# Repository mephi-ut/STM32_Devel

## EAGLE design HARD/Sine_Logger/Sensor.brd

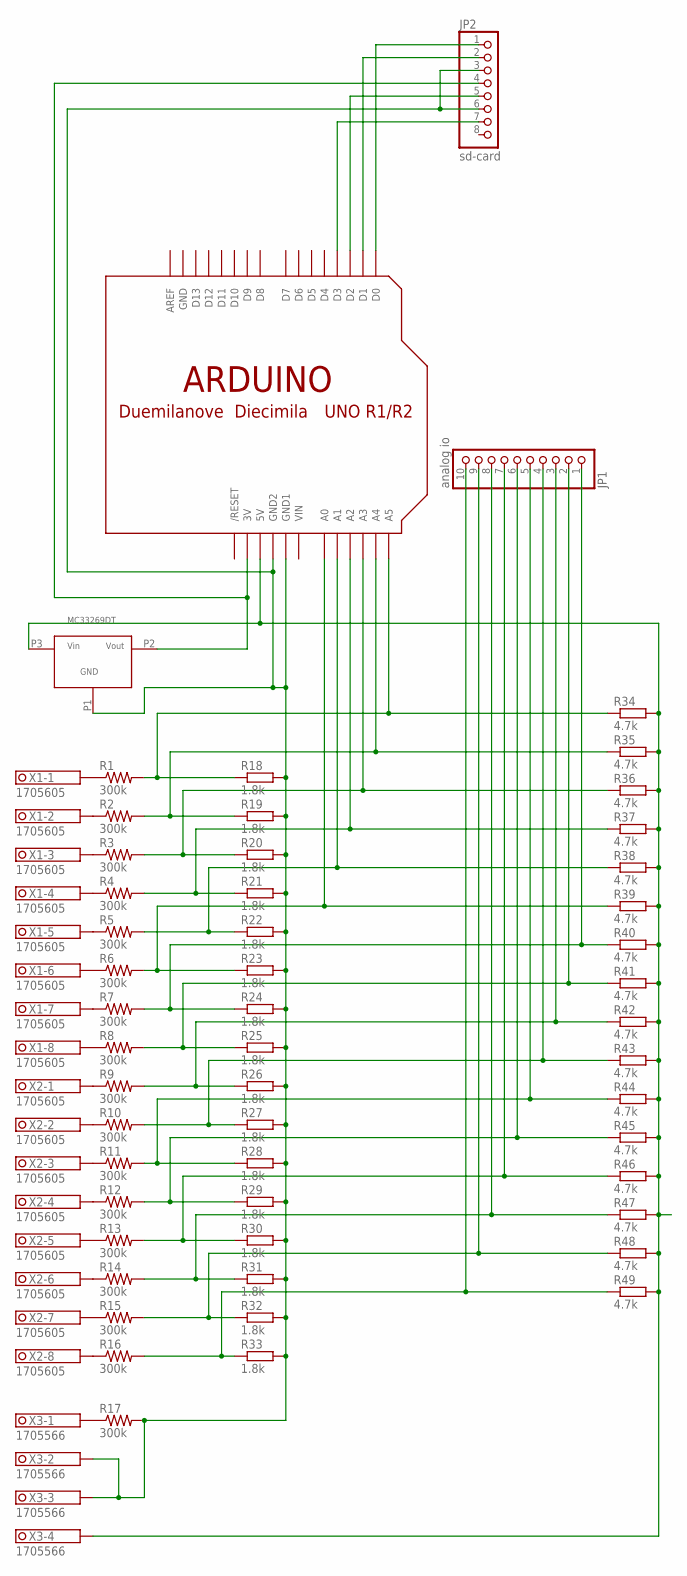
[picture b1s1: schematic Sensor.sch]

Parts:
JP1: analog io; 1X10
JP2: sd-card; 1X08
R1, R2, R3, R4, R5, R6, R7, R8, R9, R10, R11, R12, R13, R14, R15, R16, R17: 300k; 0207/15
R18, R19, R20, R21, R22, R23, R24, R25, R26, R27, R28, R29, R30, R31, R32, R33: 1.8k; R1206
R34, R35, R36, R37, R38, R39, R40, R41, R42, R43, R44, R45, R46, R47, R48, R49: 4.7k; R1206
U$1: MC33269DT
U$2: ARDUINOUNO; ARDUINO
X1, X2: 1705605
X3: 1705566

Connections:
GND: U$2.GND
unnamed: R1.1, X1.1.1, X1.1.2
unnamed: R2.1, X1.2.1, X1.2.2
unnamed: R3.1, X1.3.1, X1.3.2
unnamed: R4.1, X1.4.1, X1.4.2
unnamed: R5.1, X1.5.1, X1.5.2
unnamed: R6.1, X1.6.1, X1.6.2
unnamed: R7.1, X1.7.1, X1.7.2
unnamed: R8.1, X1.8.1, X1.8.2
unnamed: R9.1, X2.1.1, X2.1.2
unnamed: R10.1, X2.2.1, X2.2.2
unnamed: R11.1, X2.3.1, X2.3.2
unnamed: R12.1, X2.4.1, X2.4.2
unnamed: R13.1, X2.5.1, X2.5.2
unnamed: R14.1, X2.6.1, X2.6.2
unnamed: R15.1, X2.7.1, X2.7.2
unnamed: R16.1, X2.8.1, X2.8.2
unnamed: R17.1, X3.1.1, X3.1.2
unnamed: R1.2, R18.1, R34.1, U$2.A5
unnamed: R2.2, R19.1, R35.1, U$2.A4
unnamed: R3.2, R20.1, R36.1, U$2.A3
unnamed: R4.2, R21.1, R37.1, U$2.A2
unnamed: R5.2, R22.1, R38.1, U$2.A1
unnamed: R6.2, R23.1, R39.1, U$2.A0
unnamed: JP1.1, R7.2, R24.1, R40.1
unnamed: JP1.2, R8.2, R25.1, R41.1
unnamed: JP1.3, R9.2, R26.1, R42.1
unnamed: JP1.4, R10.2, R27.1, R43.1
unnamed: JP1.5, R11.2, R28.1, R44.1
unnamed: JP1.6, R12.2, R29.1, R45.1
unnamed: JP1.7, R13.2, R30.1, R46.1
unnamed: JP1.8, R14.2, R31.1, R47.1
unnamed: JP1.9, R15.2, R32.1, R48.1
unnamed: JP1.10, R16.2, R33.1, R49.1
unnamed: R34.2, R35.2, R36.2, R37.2, R38.2, R39.2, R40.2, R41.2, R42.2, R43.2, R44.2, R45.2, R46.2, R47.2, R48.2, R49.2, U$1.P3 (VIN), U$2.5V, X3.4.1, X3.4.2
unnamed: JP2.1, U$2.D0
unnamed: JP2.2, U$2.D1
unnamed: JP2.5, U$2.D2
unnamed: JP2.7, U$2.D3
unnamed: JP2.4, U$1.P2 (VOUT), U$2.3V
unnamed: JP2.3, JP2.6, R17.2, R18.2, R19.2, R20.2, R21.2, R22.2, R23.2, R24.2, R25.2, R26.2, R27.2, R28.2, R29.2, R30.2, R31.2, R32.2, R33.2, U$1.P1 (GND), U$2.GND1, U$2.GND2, X3.2.1, X3.2.2, X3.3.1, X3.3.2
VIN: U$2.VIN

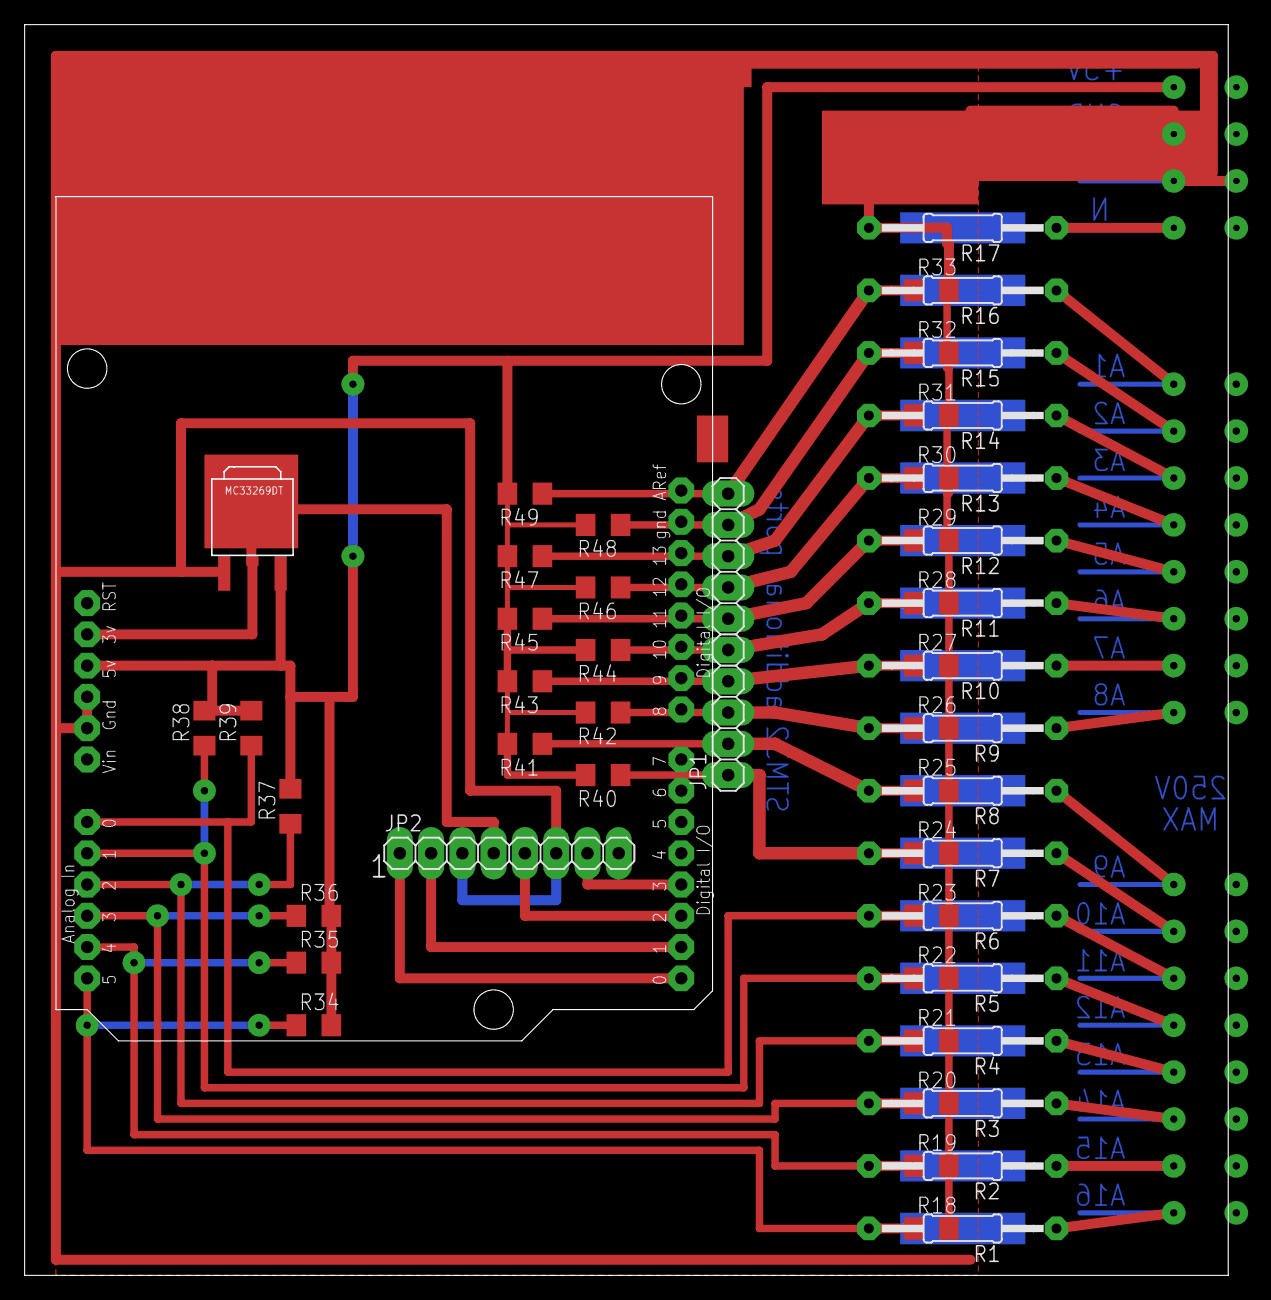
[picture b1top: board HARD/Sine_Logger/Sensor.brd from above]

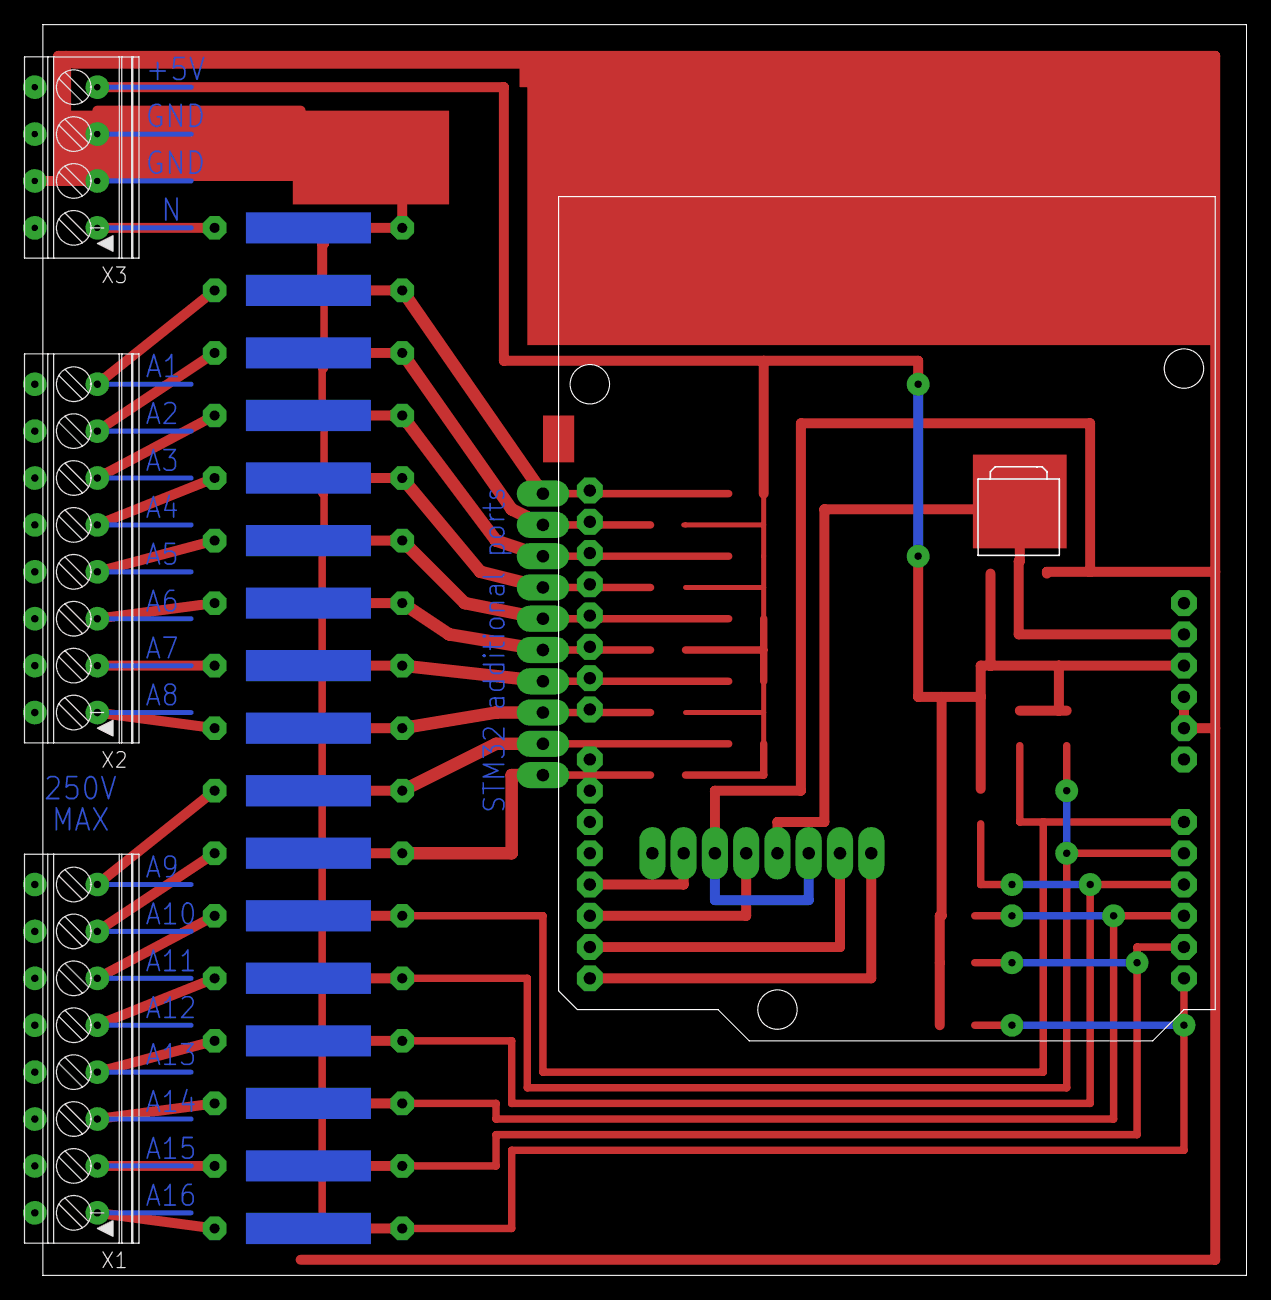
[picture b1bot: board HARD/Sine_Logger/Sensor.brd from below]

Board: 2 copper layers, 97.8 x 101.6 mm, 56 parts (3 on the bottom side), 40 nets.

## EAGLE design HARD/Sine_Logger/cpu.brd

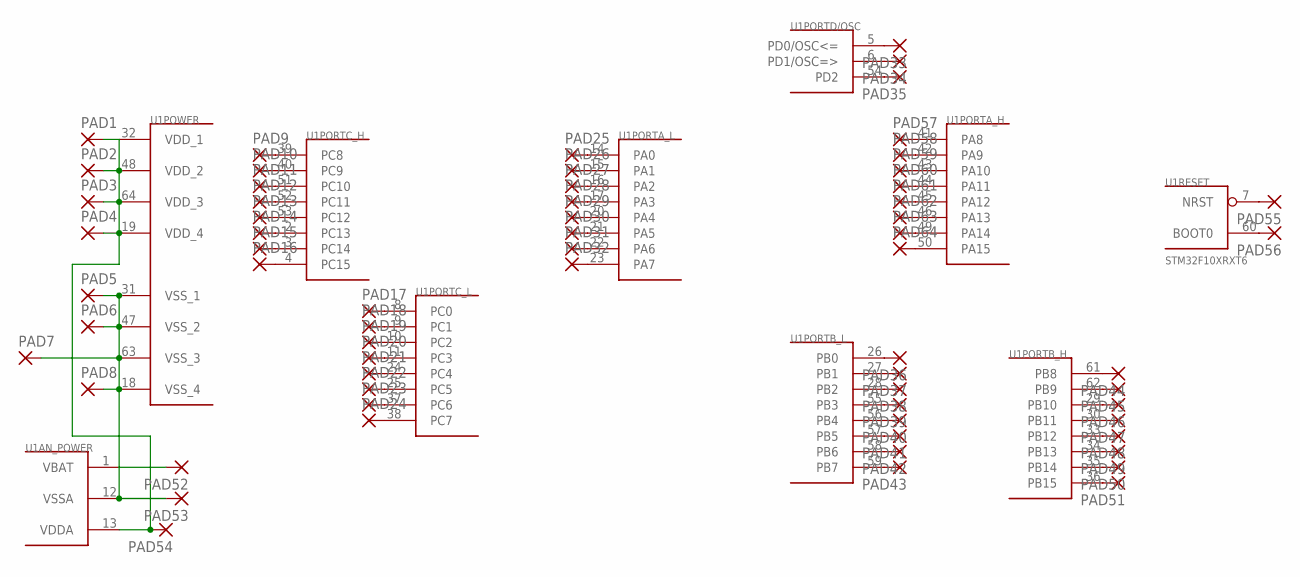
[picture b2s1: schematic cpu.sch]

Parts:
PAD1, PAD2, PAD3, PAD4, PAD5, PAD6, PAD7, PAD8, PAD9, PAD10, PAD11, PAD12, PAD13, PAD14, PAD15, PAD16, PAD17, PAD18, PAD19, PAD20, PAD21, PAD22, PAD23, PAD24, PAD25, PAD26, PAD27, PAD28, PAD29, PAD30, PAD31, PAD32, PAD33, PAD34, PAD35, PAD36, PAD37, PAD38, PAD39, PAD40, PAD41, PAD42, PAD43, PAD44, PAD45, PAD46, PAD47, PAD48, PAD49, PAD50, PAD51, PAD52, PAD53, PAD54, PAD55, PAD56, PAD57, PAD58, PAD59, PAD60, PAD61, PAD62, PAD63, PAD64: SMD2; SMD1,27-2,54
U1: STM32F10XRXT6; TQFP64

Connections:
unnamed: PAD1.1, PAD2.1, PAD3.1, PAD4.1, PAD54.1, U1.13 (VDDA), U1.19 (VDD_4), U1.32 (VDD_1), U1.48 (VDD_2), U1.64 (VDD_3)
unnamed: PAD57.1, U1.41 (PA8)
unnamed: PAD58.1, U1.42 (PA9)
unnamed: PAD59.1, U1.43 (PA10)
unnamed: PAD5.1, PAD6.1, PAD7.1, PAD8.1, PAD53.1, U1.12 (VSSA), U1.18 (VSS_4), U1.31 (VSS_1), U1.47 (VSS_2), U1.63 (VSS_3)
unnamed: PAD60.1, U1.44 (PA11)
unnamed: PAD61.1, U1.45 (PA12)
unnamed: PAD62.1, U1.46 (PA13)
unnamed: PAD9.1, U1.39 (PC8)
unnamed: PAD10.1, U1.40 (PC9)
unnamed: PAD11.1, U1.51 (PC10)
unnamed: PAD12.1, U1.52 (PC11)
unnamed: PAD13.1, U1.53 (PC12)
unnamed: PAD14.1, U1.2 (PC13)
unnamed: PAD15.1, U1.3 (PC14)
unnamed: PAD16.1, U1.4 (PC15)
unnamed: PAD17.1, U1.8 (PC0)
unnamed: PAD18.1, U1.9 (PC1)
unnamed: PAD19.1, U1.10 (PC2)
unnamed: PAD20.1, U1.11 (PC3)
unnamed: PAD21.1, U1.24 (PC4)
unnamed: PAD22.1, U1.25 (PC5)
unnamed: PAD23.1, U1.37 (PC6)
unnamed: PAD24.1, U1.38 (PC7)
unnamed: PAD25.1, U1.14 (PA0)
unnamed: PAD26.1, U1.15 (PA1)
unnamed: PAD27.1, U1.16 (PA2)
unnamed: PAD28.1, U1.17 (PA3)
unnamed: PAD29.1, U1.20 (PA4)
unnamed: PAD30.1, U1.21 (PA5)
unnamed: PAD31.1, U1.22 (PA6)
unnamed: PAD32.1, U1.23 (PA7)
unnamed: PAD33.1, U1.5 (PD0/OSC<=)
unnamed: PAD34.1, U1.6 (PD1/OSC=>)
unnamed: PAD35.1, U1.54 (PD2)
unnamed: PAD36.1, U1.26 (PB0)
unnamed: PAD37.1, U1.27 (PB1)
unnamed: PAD38.1, U1.28 (PB2)
unnamed: PAD39.1, U1.55 (PB3)
unnamed: PAD40.1, U1.56 (PB4)
unnamed: PAD41.1, U1.57 (PB5)
unnamed: PAD42.1, U1.58 (PB6)
unnamed: PAD43.1, U1.59 (PB7)
unnamed: PAD44.1, U1.61 (PB8)
unnamed: PAD45.1, U1.62 (PB9)
unnamed: PAD46.1, U1.29 (PB10)
unnamed: PAD47.1, U1.30 (PB11)
unnamed: PAD48.1, U1.33 (PB12)
unnamed: PAD49.1, U1.34 (PB13)
unnamed: PAD50.1, U1.35 (PB14)
unnamed: PAD51.1, U1.36 (PB15)
unnamed: PAD52.1, U1.1 (VBAT)
unnamed: PAD63.1, U1.49 (PA14)
unnamed: PAD64.1, U1.50 (PA15)
unnamed: PAD55.1, U1.7 (NRST)
unnamed: PAD56.1, U1.60 (BOOT0)

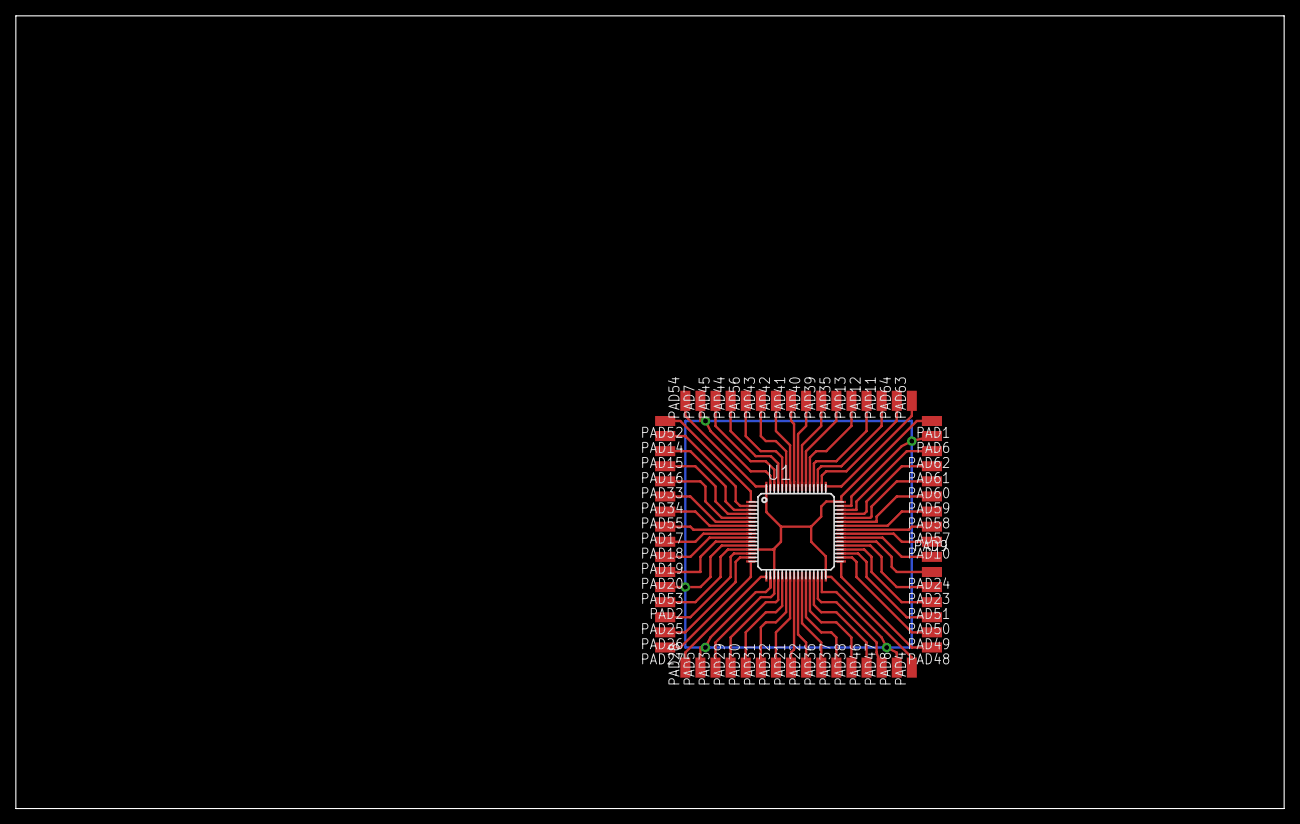
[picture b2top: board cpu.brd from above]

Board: 2 copper layers, 160.0 x 100.0 mm, 65 parts (0 on the bottom side), 56 nets.

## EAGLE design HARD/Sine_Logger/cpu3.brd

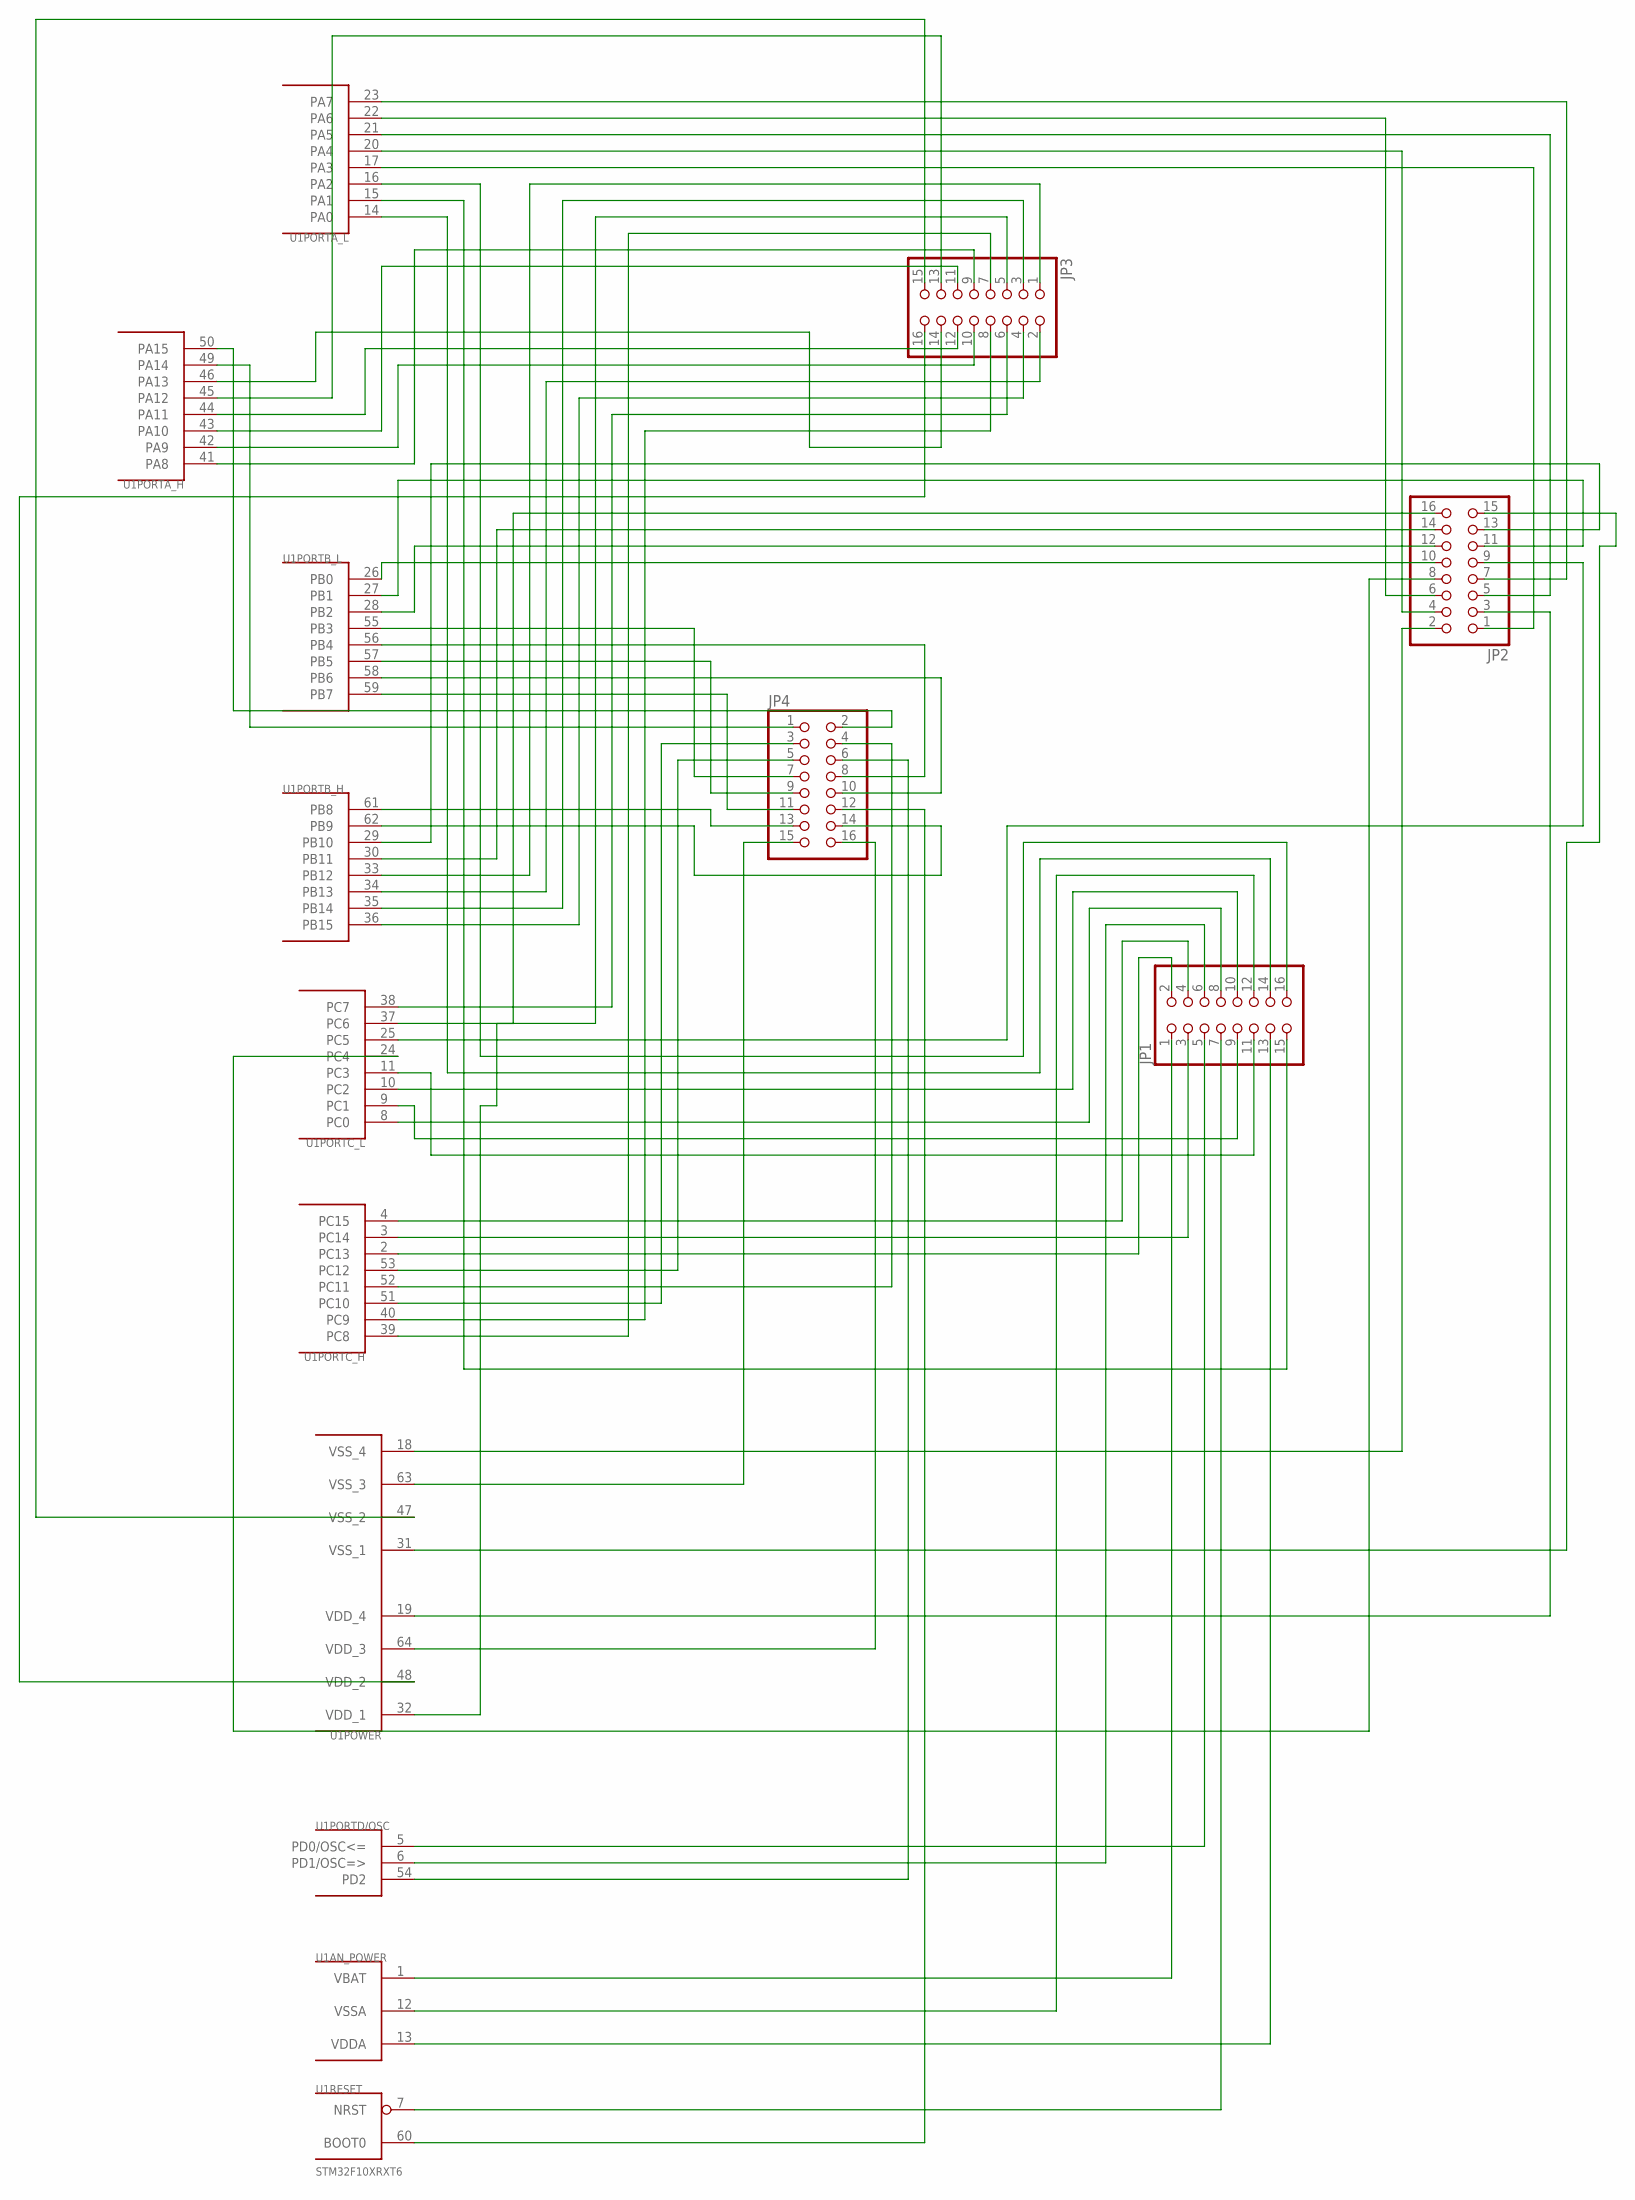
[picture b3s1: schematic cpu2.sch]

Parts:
JP1, JP2, JP3, JP4: PINHD-2X8; 2X08
U1: STM32F10XRXT6; TQFP64

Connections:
unnamed: JP1.1, U1.1 (VBAT)
unnamed: JP1.2, U1.2 (PC13)
unnamed: JP1.3, U1.3 (PC14)
unnamed: JP1.4, U1.4 (PC15)
unnamed: JP1.5, U1.5 (PD0/OSC<=)
unnamed: JP1.6, U1.6 (PD1/OSC=>)
unnamed: JP1.7, U1.7 (NRST)
unnamed: JP1.8, U1.8 (PC0)
unnamed: JP1.9, U1.9 (PC1)
unnamed: JP1.10, U1.10 (PC2)
unnamed: JP1.11, U1.11 (PC3)
unnamed: JP1.12, U1.12 (VSSA)
unnamed: JP1.13, U1.13 (VDDA)
unnamed: JP1.14, U1.14 (PA0)
unnamed: JP1.15, U1.15 (PA1)
unnamed: JP1.16, U1.16 (PA2)
unnamed: JP2.1, U1.17 (PA3)
unnamed: JP2.2, U1.18 (VSS_4)
unnamed: JP2.3, U1.19 (VDD_4)
unnamed: JP2.4, U1.20 (PA4)
unnamed: JP2.5, U1.21 (PA5)
unnamed: JP2.6, U1.22 (PA6)
unnamed: JP2.7, U1.23 (PA7)
unnamed: JP2.8, U1.24 (PC4)
unnamed: JP2.9, U1.25 (PC5)
unnamed: JP2.10, U1.26 (PB0)
unnamed: JP2.11, U1.27 (PB1)
unnamed: JP2.12, U1.28 (PB2)
unnamed: JP2.13, U1.29 (PB10)
unnamed: JP2.14, U1.30 (PB11)
unnamed: JP2.15, U1.31 (VSS_1)
unnamed: JP2.16, U1.32 (VDD_1)
unnamed: JP3.1, U1.33 (PB12)
unnamed: JP3.2, U1.34 (PB13)
unnamed: JP3.3, U1.35 (PB14)
unnamed: JP3.4, U1.36 (PB15)
unnamed: JP3.5, U1.37 (PC6)
unnamed: JP3.6, U1.38 (PC7)
unnamed: JP3.7, U1.39 (PC8)
unnamed: JP3.8, U1.40 (PC9)
unnamed: JP3.9, U1.41 (PA8)
unnamed: JP3.10, U1.42 (PA9)
unnamed: JP3.11, U1.43 (PA10)
unnamed: JP3.12, U1.44 (PA11)
unnamed: JP3.13, U1.45 (PA12)
unnamed: JP3.14, U1.46 (PA13)
unnamed: JP3.15, U1.47 (VSS_2)
unnamed: JP3.16, U1.48 (VDD_2)
unnamed: JP4.1, U1.49 (PA14)
unnamed: JP4.2, U1.50 (PA15)
unnamed: JP4.3, U1.51 (PC10)
unnamed: JP4.4, U1.52 (PC11)
unnamed: JP4.5, U1.53 (PC12)
unnamed: JP4.6, U1.54 (PD2)
unnamed: JP4.7, U1.55 (PB3)
unnamed: JP4.8, U1.56 (PB4)
unnamed: JP4.9, U1.57 (PB5)
unnamed: JP4.10, U1.58 (PB6)
unnamed: JP4.11, U1.59 (PB7)
unnamed: JP4.12, U1.60 (BOOT0)
unnamed: JP4.13, U1.61 (PB8)
unnamed: JP4.14, U1.62 (PB9)
unnamed: JP4.15, U1.63 (VSS_3)
unnamed: JP4.16, U1.64 (VDD_3)

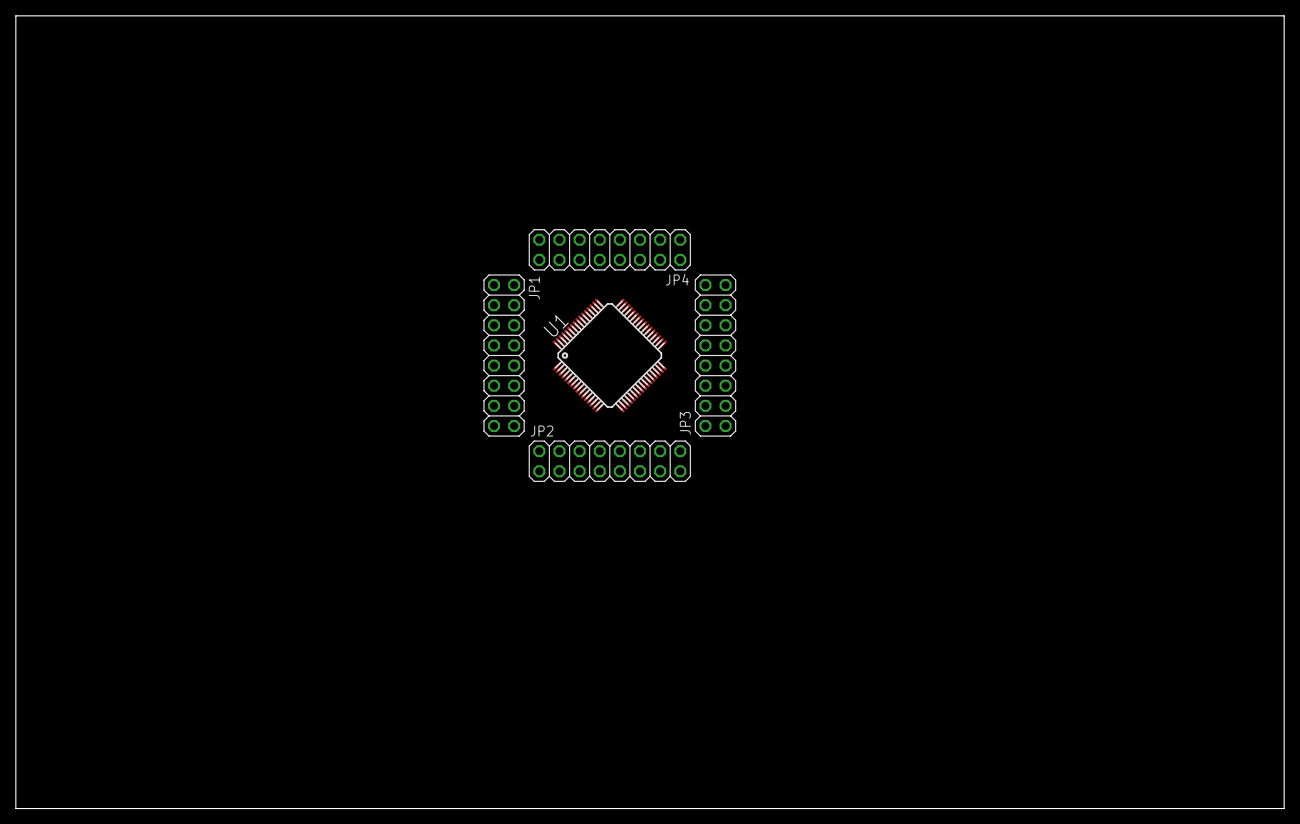
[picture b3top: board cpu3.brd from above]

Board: 2 copper layers, 160.0 x 100.0 mm, 5 parts (0 on the bottom side), 64 nets.

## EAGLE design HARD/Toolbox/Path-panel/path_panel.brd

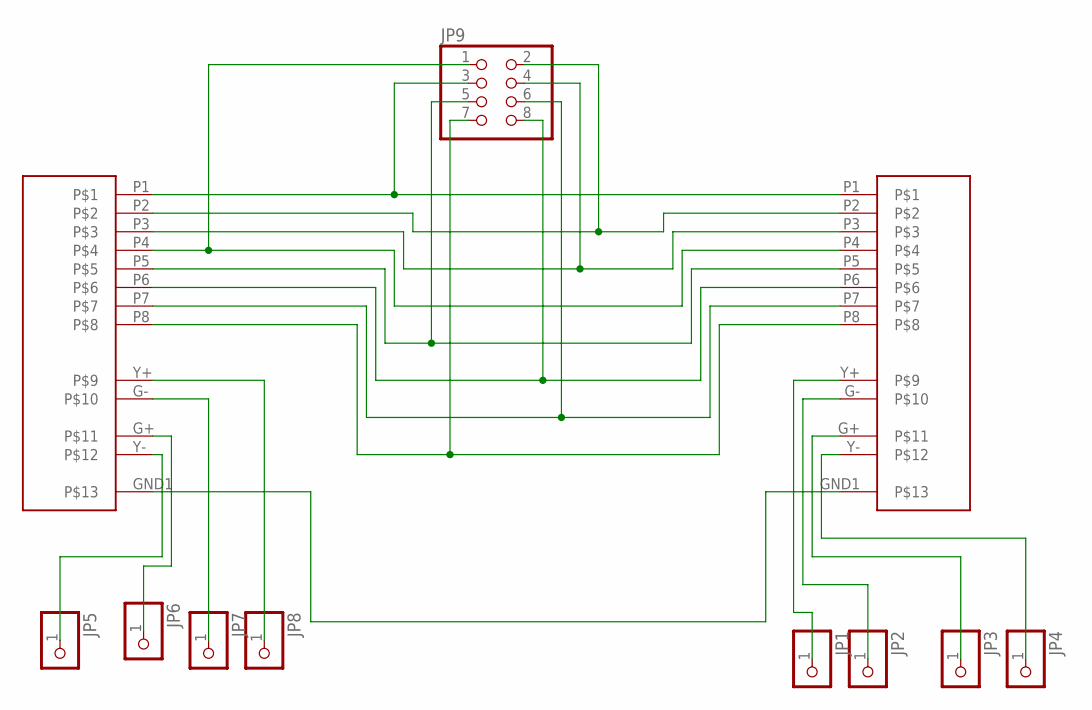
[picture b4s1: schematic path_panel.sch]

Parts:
JP1, JP2, JP3, JP4, JP5, JP6, JP7, JP8: PINHD-1X1; 1X01
JP9: PINHD-2X4; 2X04
U$14, U$15: RJ-45_LEDS

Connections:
unnamed: JP9.3, U$14.P1, U$15.P1
unnamed: U$14.GND1, U$15.GND1
unnamed: JP5.1, U$14.Y-
unnamed: JP6.1, U$14.G+
unnamed: JP7.1, U$14.G-
unnamed: JP8.1, U$14.Y+
unnamed: JP4.1, U$15.Y-
unnamed: JP3.1, U$15.G+
unnamed: JP2.1, U$15.G-
unnamed: JP1.1, U$15.Y+
unnamed: JP9.2, U$14.P2, U$15.P2
unnamed: JP9.4, U$14.P3, U$15.P3
unnamed: JP9.1, U$14.P4, U$15.P4
unnamed: JP9.5, U$14.P5, U$15.P5
unnamed: JP9.8, U$14.P6, U$15.P6
unnamed: JP9.6, U$14.P7, U$15.P7
unnamed: JP9.7, U$14.P8, U$15.P8

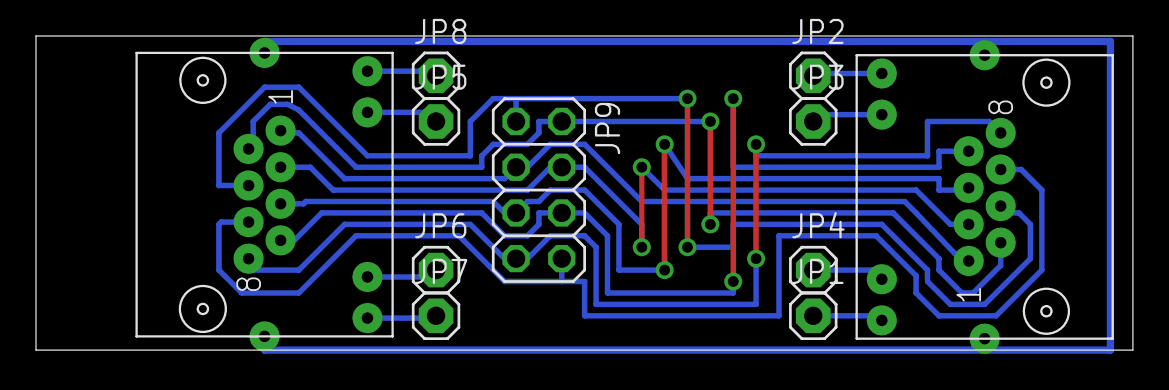
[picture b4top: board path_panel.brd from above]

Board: 2 copper layers, 60.9 x 17.4 mm, 11 parts (0 on the bottom side), 17 nets.

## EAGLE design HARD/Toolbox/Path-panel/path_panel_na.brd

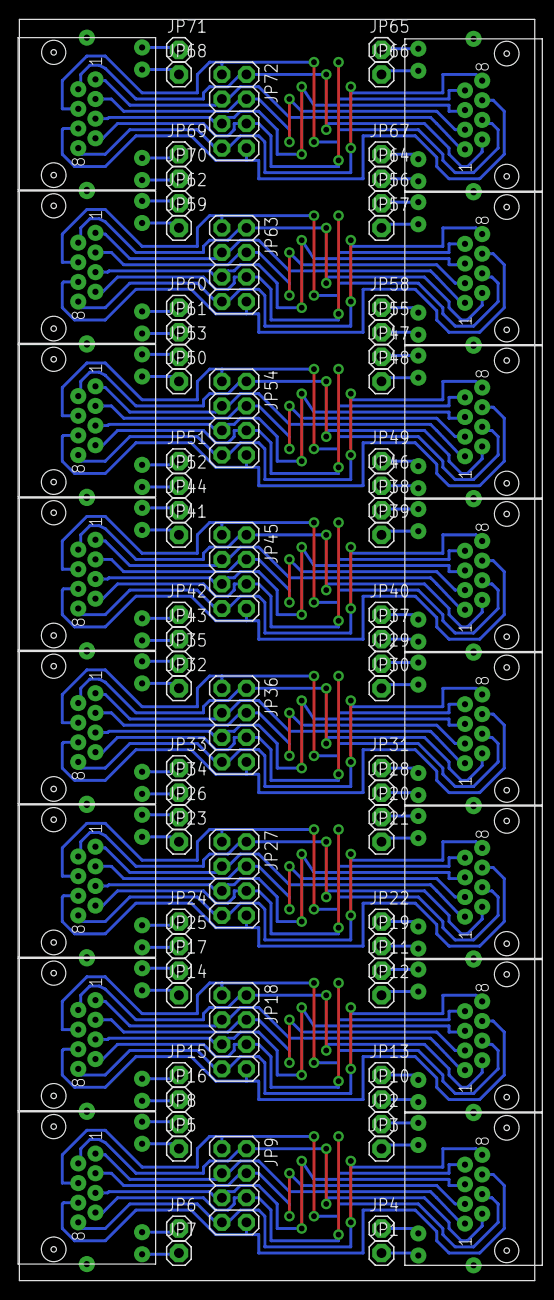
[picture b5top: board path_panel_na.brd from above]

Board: 2 copper layers, 53.3 x 130.5 mm, 88 parts (0 on the bottom side), 136 nets.

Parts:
JP1, JP2, JP3, JP4, JP5, JP6, JP7, JP8, JP10, JP11, JP12, JP13, JP14, JP15, JP16, JP17, JP19, JP20, JP21, JP22, JP23, JP24, JP25, JP26, JP28, JP29, JP30, JP31, JP32, JP33, JP34, JP35, JP37, JP38, JP39, JP40, JP41, JP42, JP43, JP44, JP46, JP47, JP48, JP49, JP50, JP51, JP52, JP53, JP55, JP56, JP57, JP58, JP59, JP60, JP61, JP62, JP64, JP65, JP66, JP67, JP68, JP69, JP70, JP71: 1X01
JP9, JP18, JP27, JP36, JP45, JP54, JP63, JP72: 2X04
U$1, U$2, U$3, U$4, U$5, U$6, U$7, U$8, U$9, U$10, U$11, U$12, U$13, U$14, U$15, U$16: RJ-45_LEDS

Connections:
unnamed: JP9.3, U$14.P1, U$15.P1
unnamed: U$14.GND1, U$15.GND1
unnamed: JP5.1, U$14.Y-
unnamed: JP6.1, U$14.G+
unnamed: JP7.1, U$14.G-
unnamed: JP8.1, U$14.Y+
unnamed: JP4.1, U$15.Y-
unnamed: JP3.1, U$15.G+
unnamed: JP2.1, U$15.G-
unnamed: JP1.1, U$15.Y+
unnamed: JP18.3, U$1.P1, U$2.P1
unnamed: JP18.2, U$1.P2, U$2.P2
unnamed: JP18.4, U$1.P3, U$2.P3
unnamed: JP9.2, U$14.P2, U$15.P2
unnamed: JP9.4, U$14.P3, U$15.P3
unnamed: JP9.1, U$14.P4, U$15.P4
unnamed: JP9.5, U$14.P5, U$15.P5
unnamed: JP9.8, U$14.P6, U$15.P6
unnamed: JP9.6, U$14.P7, U$15.P7
unnamed: JP9.7, U$14.P8, U$15.P8
unnamed: JP18.1, U$1.P4, U$2.P4
unnamed: JP18.5, U$1.P5, U$2.P5
unnamed: JP18.8, U$1.P6, U$2.P6
unnamed: JP18.6, U$1.P7, U$2.P7
unnamed: JP18.7, U$1.P8, U$2.P8
unnamed: U$1.GND1, U$2.GND1
unnamed: JP14.1, U$1.Y-
unnamed: JP15.1, U$1.G+
unnamed: JP16.1, U$1.G-
unnamed: JP17.1, U$1.Y+
unnamed: JP13.1, U$2.Y-
unnamed: JP12.1, U$2.G+
unnamed: JP11.1, U$2.G-
unnamed: JP10.1, U$2.Y+
unnamed: JP27.3, U$3.P1, U$4.P1
unnamed: JP27.2, U$3.P2, U$4.P2
unnamed: JP27.4, U$3.P3, U$4.P3
unnamed: JP27.1, U$3.P4, U$4.P4
unnamed: JP27.5, U$3.P5, U$4.P5
unnamed: JP27.8, U$3.P6, U$4.P6
unnamed: JP27.6, U$3.P7, U$4.P7
unnamed: JP27.7, U$3.P8, U$4.P8
unnamed: U$3.GND1, U$4.GND1
unnamed: JP23.1, U$3.Y-
unnamed: JP24.1, U$3.G+
unnamed: JP25.1, U$3.G-
unnamed: JP26.1, U$3.Y+
unnamed: JP22.1, U$4.Y-
unnamed: JP21.1, U$4.G+
unnamed: JP20.1, U$4.G-
unnamed: JP19.1, U$4.Y+
unnamed: JP36.3, U$5.P1, U$6.P1
unnamed: JP36.2, U$5.P2, U$6.P2
unnamed: JP36.4, U$5.P3, U$6.P3
unnamed: JP36.1, U$5.P4, U$6.P4
unnamed: JP36.5, U$5.P5, U$6.P5
unnamed: JP36.8, U$5.P6, U$6.P6
unnamed: JP36.6, U$5.P7, U$6.P7
unnamed: JP36.7, U$5.P8, U$6.P8
unnamed: U$5.GND1, U$6.GND1
unnamed: JP32.1, U$5.Y-
unnamed: JP33.1, U$5.G+
unnamed: JP34.1, U$5.G-
unnamed: JP35.1, U$5.Y+
unnamed: JP31.1, U$6.Y-
unnamed: JP30.1, U$6.G+
unnamed: JP29.1, U$6.G-
unnamed: JP28.1, U$6.Y+
unnamed: JP45.3, U$7.P1, U$8.P1
unnamed: JP45.2, U$7.P2, U$8.P2
unnamed: JP45.4, U$7.P3, U$8.P3
unnamed: JP45.1, U$7.P4, U$8.P4
unnamed: JP45.5, U$7.P5, U$8.P5
unnamed: JP45.8, U$7.P6, U$8.P6
unnamed: JP45.6, U$7.P7, U$8.P7
unnamed: JP45.7, U$7.P8, U$8.P8
unnamed: U$7.GND1, U$8.GND1
unnamed: JP41.1, U$7.Y-
unnamed: JP42.1, U$7.G+
unnamed: JP43.1, U$7.G-
unnamed: JP44.1, U$7.Y+
unnamed: JP40.1, U$8.Y-
unnamed: JP39.1, U$8.G+
unnamed: JP38.1, U$8.G-
unnamed: JP37.1, U$8.Y+
unnamed: JP54.3, U$9.P1, U$10.P1
unnamed: JP54.2, U$9.P2, U$10.P2
unnamed: JP54.4, U$9.P3, U$10.P3
unnamed: JP54.1, U$9.P4, U$10.P4
unnamed: JP54.5, U$9.P5, U$10.P5
unnamed: JP54.8, U$9.P6, U$10.P6
unnamed: JP54.6, U$9.P7, U$10.P7
unnamed: JP54.7, U$9.P8, U$10.P8
unnamed: U$9.GND1, U$10.GND1
unnamed: JP50.1, U$9.Y-
unnamed: JP51.1, U$9.G+
unnamed: JP52.1, U$9.G-
unnamed: JP53.1, U$9.Y+
unnamed: JP49.1, U$10.Y-
unnamed: JP48.1, U$10.G+
unnamed: JP47.1, U$10.G-
unnamed: JP46.1, U$10.Y+
unnamed: JP63.3, U$11.P1, U$12.P1
unnamed: JP63.2, U$11.P2, U$12.P2
unnamed: JP63.4, U$11.P3, U$12.P3
unnamed: JP63.1, U$11.P4, U$12.P4
unnamed: JP63.5, U$11.P5, U$12.P5
unnamed: JP63.8, U$11.P6, U$12.P6
unnamed: JP63.6, U$11.P7, U$12.P7
unnamed: JP63.7, U$11.P8, U$12.P8
unnamed: U$11.GND1, U$12.GND1
unnamed: JP59.1, U$11.Y-
unnamed: JP60.1, U$11.G+
unnamed: JP61.1, U$11.G-
unnamed: JP62.1, U$11.Y+
unnamed: JP58.1, U$12.Y-
unnamed: JP57.1, U$12.G+
unnamed: JP56.1, U$12.G-
unnamed: JP55.1, U$12.Y+
unnamed: JP72.3, U$13.P1, U$16.P1
unnamed: JP72.2, U$13.P2, U$16.P2
unnamed: JP72.4, U$13.P3, U$16.P3
unnamed: JP72.1, U$13.P4, U$16.P4
unnamed: JP72.5, U$13.P5, U$16.P5
unnamed: JP72.8, U$13.P6, U$16.P6
unnamed: JP72.6, U$13.P7, U$16.P7
unnamed: JP72.7, U$13.P8, U$16.P8
unnamed: U$13.GND1, U$16.GND1
unnamed: JP68.1, U$13.Y-
unnamed: JP69.1, U$13.G+
unnamed: JP70.1, U$13.G-
unnamed: JP71.1, U$13.Y+
unnamed: JP67.1, U$16.Y-
unnamed: JP66.1, U$16.G+
unnamed: JP65.1, U$16.G-
unnamed: JP64.1, U$16.Y+

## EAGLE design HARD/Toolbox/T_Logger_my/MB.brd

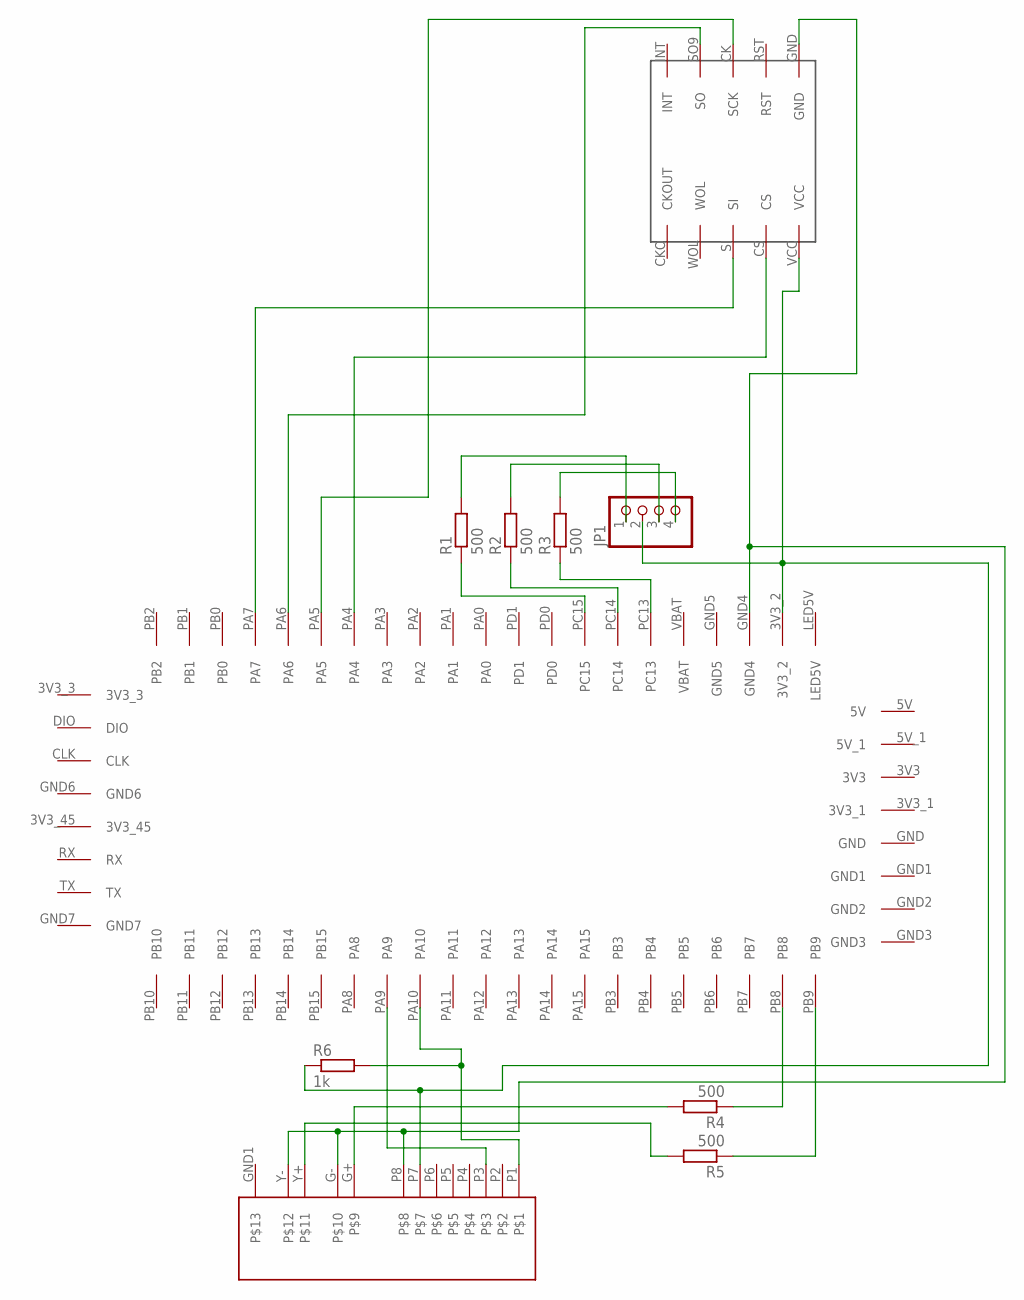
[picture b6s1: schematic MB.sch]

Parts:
JP1: PINHD-1X4; 1X04
R1, R2, R3, R4, R5: 500; M1206
R6: 1k; M1206
U$1: F100X_SYSBOARD; F10X_SYSBOARD
U$2: SPI_ETHERNET
U$3: RJ-45_LEDS

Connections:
3V3: U$1.3V3
3V3_1: U$1.3V3_1
5V: U$1.5V
5V_1: U$1.5V_1
GND: U$1.GND
GND1: U$1.GND1
GND5: U$1.GND5
LED5V: U$1.LED5V
unnamed: U$1.PA4, U$2.CS
unnamed: U$1.PA6, U$2.SO9 (SO)
unnamed: U$1.PA7, U$2.SI
unnamed: U$1.PA5, U$2.CK (SCK)
unnamed: JP1.2, R6.1, U$1.3V3_2, U$2.VCC, U$3.P7
unnamed: U$1.GND4, U$2.GND, U$3.G-, U$3.P8, U$3.Y-
unnamed: JP1.4, R3.2
unnamed: JP1.3, R2.2
unnamed: JP1.1, R1.2
unnamed: R3.1, U$1.PC13
unnamed: R2.1, U$1.PC14
unnamed: R1.1, U$1.PC15
unnamed: U$1.PA9, U$3.P3
unnamed: R6.2, U$1.PA10, U$3.P1
unnamed: R4.1, U$1.PB8
unnamed: R4.2, U$3.G+
unnamed: R5.1, U$1.PB9
unnamed: R5.2, U$3.Y+
P$13: U$3.GND1
VBAT: U$1.VBAT
